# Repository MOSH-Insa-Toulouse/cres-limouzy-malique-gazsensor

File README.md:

# Capteur intelligent de gaz monté sur une Arduino Uno
Dans le cadre du cours "Microcontrolleurs et open-source hardware" de 5ème année ISS (Innovative Smart System) à l'INSA de Toulouse, nous avons réalisé un shield Arduino incluant une carte Lora afin de faire transiter les informations issues de divers capteurs sur ledit réseau bas débit. Le projet se décompose en plusieurs parties :
* Création du shield Arduino Uno sous KiCad incluant :
  - la puce Lora RN2483 et son antenne associée
  - le capteur de gaz MQ2 avec connectique GROVE
  - un capteur de gaz "maison" et son étage d'amplification
  - deux LEDs
* Développement d'un programme sous l'IDE Arduino permettant de récupérer les informations issues de divers capteurs branchés sur l'Arduino et les transmettre sur le réseau basse consommation Lora nommé TheThingsNetwork.
* Création d'une interface web affichant les informations issues du capteur de gaz sous la forme d'un graphe, grâce à node-red.

# Prérequis
* Software
	- Arduino IDE avec les bibliothéques SoftwareSerial et TheThingsNetwork
	- Un compte TheThingsNetwork
	- Node-red
* Hardware
	- Un Arduino Uno
	- Un capteur de gaz MQ2 avec connecteur GROVE
	- Deux LEDs
	- Une puce Lora RN2483

# Création d'un shield pour Arduino Uno
Vous pouvez trouver les sources KiCad dans le dossier [ShieldArduinoKiCad](/ShieldArduinoKicad/).
Vous trouverez ci-dessous une vue d'ensemble de la schématique, du routage et du rendu 3D de notre shield.

# Développement du software sur Arduino Uno
Le code est distribué dans le dossier [arduino](/arduino/).
Concrétement, il implémente :
* La connexion de la carte Lora au réseau TheThingsNetwork
* La mise en place d'un mode uplink (communication Arduino --> theThingsNetwork via Lora afin d'envoyer les informations issues des capteurs)
* La mise en place d'un mode downlink (communication theThingsNetwork --> Arduino via Lora permettant de commander des LEDs via une interface web). Il est intéressant de noter que la réception d'un message sur l'arduino (message downlink) se fait uniquement après l'envoi d'un message uplink, car la puce RN2483 est un device Lora de classe A. C'est pourquoi il est obligatoire d'envoyer périodiquement une trame (manuellement à l'aide d'un *sendBytes* ou automatiquement à l'aide de la fonction *ttn.poll()*)
* La mise en place de deux LEDs, l'une indiquant un niveau de gaz trop élevé dans la pièce, l'autre permettant de tester le mode downlink

# Développement d'une interface graphique de gestion de données grâce à node-red
Node-red est un outil graphique permettant de lier plusieurs services et APIs ensemble de manière assez facile. Ainsi, nous avons créé une interface permettant d'afficher les informations issues du capteur de gaz sous forme de gauge de danger. De plus, nous avons la possibilité d'allumer, d'éteindre ou de faire clignoter la LED sur notre Arduino, à distance grâce à node-red ou l'interface theThingsNetwork. Vous trouverez ci-dessous l'interface node-red créé pour le projet ainsi que le rendu graphique final.

# FAQ software
## La connexion à TheThingsNetwork ne fonctionne pas
* Réinitialiser l'Arduino à l'aide du bouton RESET, ainsi que la carte Lora en branchant la pin RST du RN2483 sur la masse de l'arduino pendant quelques secondes
* Vérifier qu'une gateway Lora est bien présente aux alentours et que le signal est suffisamment fort pour permettre la connexion

## La connexion de node-red à TheThingsNetwork est impossible
* Vérifier que votre routeur internet ne bloque pas la connexion

## Le mode uplink ne fonctionne pas
* Vérifier que la connexion avec TheThingsNetwork est bien réalisée à l'aide de la console série Arduino
* Cliquer sur "RESET FRAME COUNTERS" sur la page de votre device sur TheThingsNetwork

## Le mode downlink ne fonctionne pas
* Vérifier que la connexion avec TheThingsNetwork est bien réalisée à l'aide de la console série Arduino
* Vérifier que votre code envoie périodiquement des trames Lora afin de permettre les messages downlink

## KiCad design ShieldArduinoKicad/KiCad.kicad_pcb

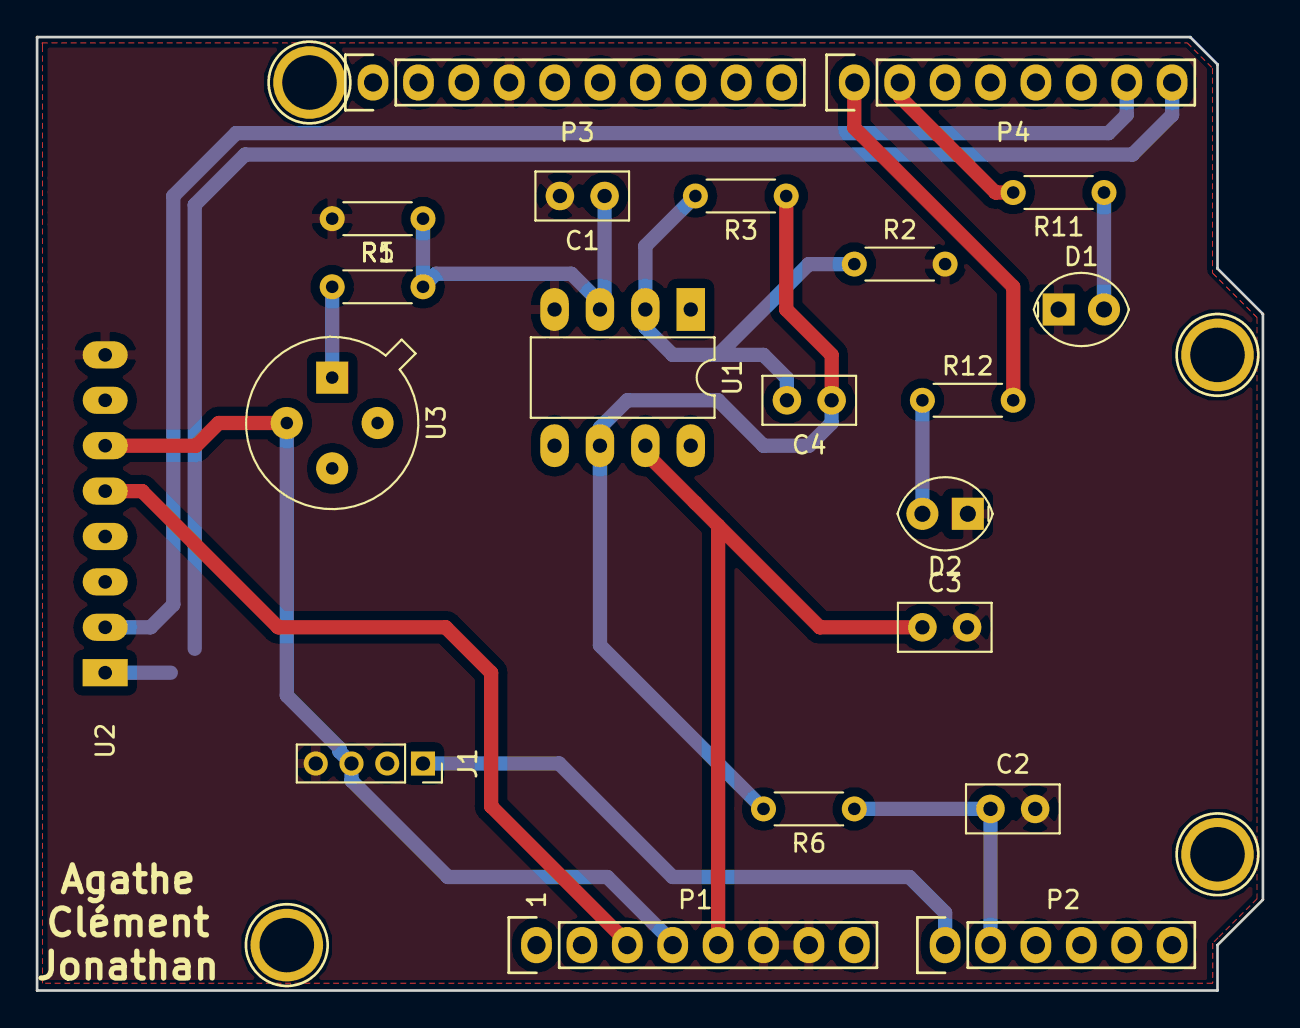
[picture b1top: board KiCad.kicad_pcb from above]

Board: 2 copper layers, 68.6 x 53.3 mm, 25 parts (0 on the bottom side), 16 nets.

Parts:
C1, C2, C3: 100n; C_Disc_D5.0mm_W2.5mm_P2.50mm
C4: 1u; C_Disc_D5.0mm_W2.5mm_P2.50mm
D1: YELLOW; LED_Oval_W5.2mm_H3.8mm
D2: RED; LED_Oval_W5.2mm_H3.8mm
J1: Conn_01x04; PinSocket_1x04_P2.00mm_Vertical
P1: Power; Socket_Strip_Arduino_1x08
P2: Analog; Socket_Strip_Arduino_1x06
P3: Digital; Socket_Strip_Arduino_1x10
P4: Digital; Socket_Strip_Arduino_1x08
P5, P6, P7, P8: CONN_01X01; Arduino_1pin
R1, R3: 100k; R_Axial_DIN0204_L3.6mm_D1.6mm_P5.08mm_Horizontal
R2, R6: 1k; R_Axial_DIN0204_L3.6mm_D1.6mm_P5.08mm_Horizontal
R5: 10k; R_Axial_DIN0204_L3.6mm_D1.6mm_P5.08mm_Horizontal
R11, R12: 150; R_Axial_DIN0204_L3.6mm_D1.6mm_P5.08mm_Horizontal
U1: LTC1050; DIP-8_W7.62mm_LongPads
U2: RN2483_Breakout; Module_RN2483_Breakout
U3: TO54

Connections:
+3V3: J1.3, P1.4, U2.6, U3.2
+5V: C3.1, P1.5, U1.7
/0(Rx): P4.8, U2.1
/1(Tx): P4.7, U2.2
/6(**): P4.2, R11.2
/7: P4.1, R12.2
/A0: J1.1, P2.1
/Reset: P1.3, U2.5
Arduino: C2.1, P2.2, R6.1
GND: C1.2, C2.2, C3.2, D1.1, D2.1, J1.4, P1.6, P1.7, P3.4, R1.2, R2.2, U1.4, U2.8
unnamed: C1.1, R1.1, R5.2, U1.3
unnamed: C4.1, R3.1, R6.2, U1.6
unnamed: C4.2, R2.1, R3.2, U1.2
unnamed: D1.2, R11.1
unnamed: D2.2, R12.1
unnamed: R5.1, U3.1

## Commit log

2018-11-28 Add files via upload
    Initial version
2018-11-28 Update README.md
    Modify pictures
2018-11-28 Update README.md
    Update pictures path
2018-11-29 Update README.md
    Update pictures' path
